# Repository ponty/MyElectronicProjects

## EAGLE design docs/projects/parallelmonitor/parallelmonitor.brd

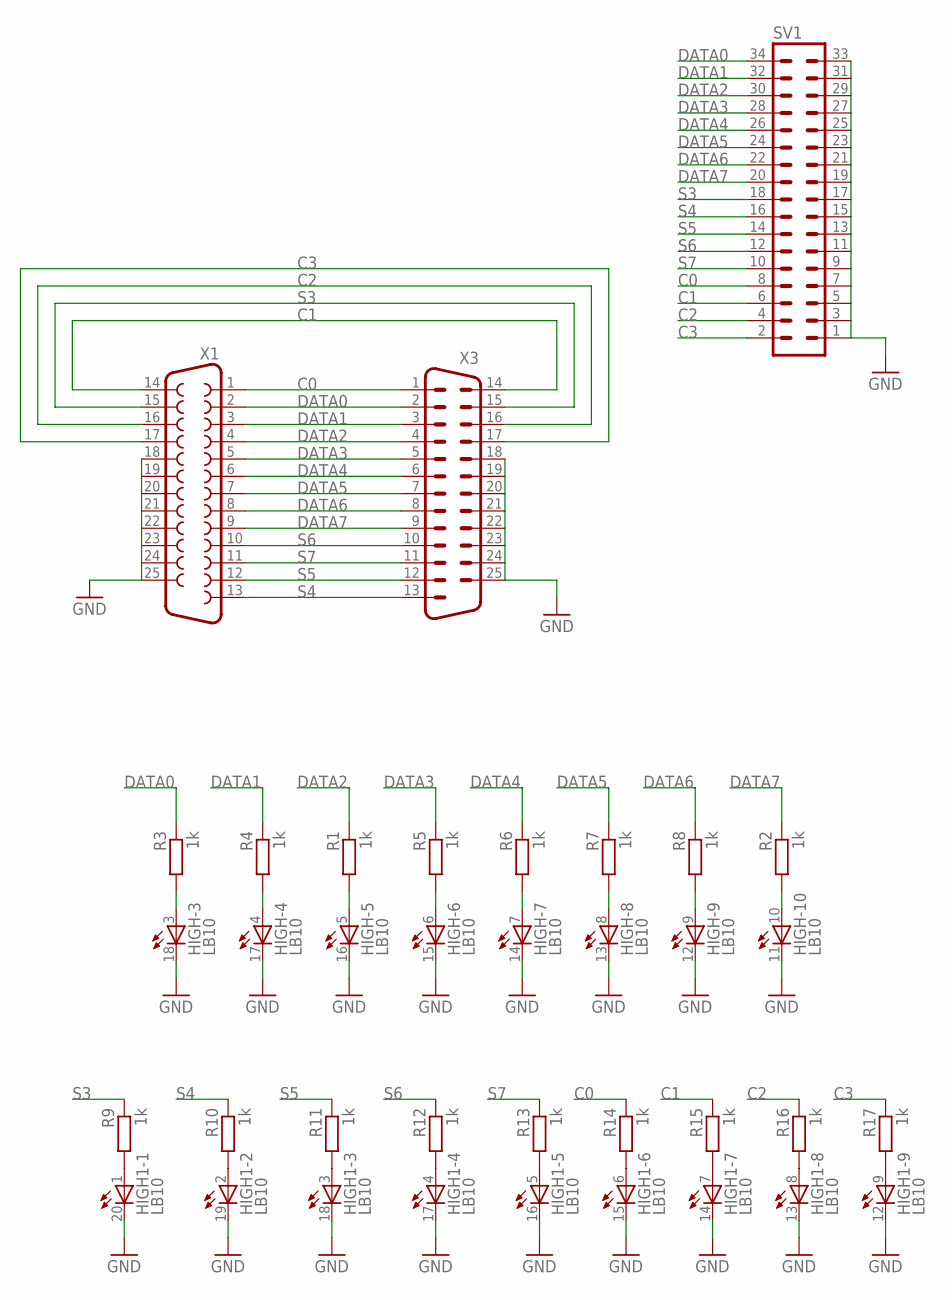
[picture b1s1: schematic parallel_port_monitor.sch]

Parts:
HIGH, HIGH1: LB10
R1, R2, R3, R4, R5, R6, R7, R8, R9, R10, R11, R12, R13, R14, R15, R16, R17: 1k; M0805
SV1: MA17-2W
X1: F25D
X3: M25D

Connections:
C0: R14.1, SV1.8, X1.1, X3.1
C1: R15.1, SV1.6, X1.14, X3.14
C2: R16.1, SV1.4, X1.16, X3.16
C3: R17.1, SV1.2, X1.17, X3.17
DATA0: R3.1, SV1.34, X1.2, X3.2
DATA1: R4.1, SV1.32, X1.3, X3.3
DATA2: R1.1, SV1.30, X1.4, X3.4
DATA3: R5.1, SV1.28, X1.5, X3.5
DATA4: R6.1, SV1.26, X1.6, X3.6
DATA5: R7.1, SV1.24, X1.7, X3.7
DATA6: R8.1, SV1.22, X1.8, X3.8
DATA7: R2.1, SV1.20, X1.9, X3.9
GND: HIGH.11 (C), HIGH.12 (C), HIGH.13 (C), HIGH.14 (C), HIGH.15 (C), HIGH.16 (C), HIGH.17 (C), HIGH.18 (C), HIGH1.12 (C), HIGH1.13 (C), HIGH1.14 (C), HIGH1.15 (C), HIGH1.16 (C), HIGH1.17 (C), HIGH1.18 (C), HIGH1.19 (C), HIGH1.20 (C), SV1.1, SV1.3, SV1.5, SV1.7, SV1.9, SV1.11, SV1.13, SV1.15, SV1.17, SV1.19, SV1.21, SV1.23, SV1.25, SV1.27, SV1.29, SV1.31, SV1.33, X1.18, X1.19, X1.20, X1.21, X1.22, X1.23, X1.24, X1.25, X3.18, X3.19, X3.20, X3.21, X3.22, X3.23, X3.24, X3.25
unnamed: HIGH.10 (A), R2.2
unnamed: HIGH1.1 (A), R9.2
unnamed: HIGH.3 (A), R3.2
unnamed: HIGH.4 (A), R4.2
unnamed: HIGH.6 (A), R5.2
unnamed: HIGH.5 (A), R1.2
unnamed: HIGH.7 (A), R6.2
unnamed: HIGH.8 (A), R7.2
unnamed: HIGH.9 (A), R8.2
unnamed: HIGH1.2 (A), R10.2
unnamed: HIGH1.3 (A), R11.2
unnamed: HIGH1.4 (A), R12.2
unnamed: HIGH1.5 (A), R13.2
unnamed: HIGH1.6 (A), R14.2
unnamed: HIGH1.7 (A), R15.2
unnamed: HIGH1.8 (A), R16.2
unnamed: HIGH1.9 (A), R17.2
S3: R9.1, SV1.18, X1.15, X3.15
S4: R10.1, SV1.16, X1.13, X3.13
S5: R11.1, SV1.14, X1.12, X3.12
S6: R12.1, SV1.12, X1.10, X3.10
S7: R13.1, SV1.10, X1.11, X3.11

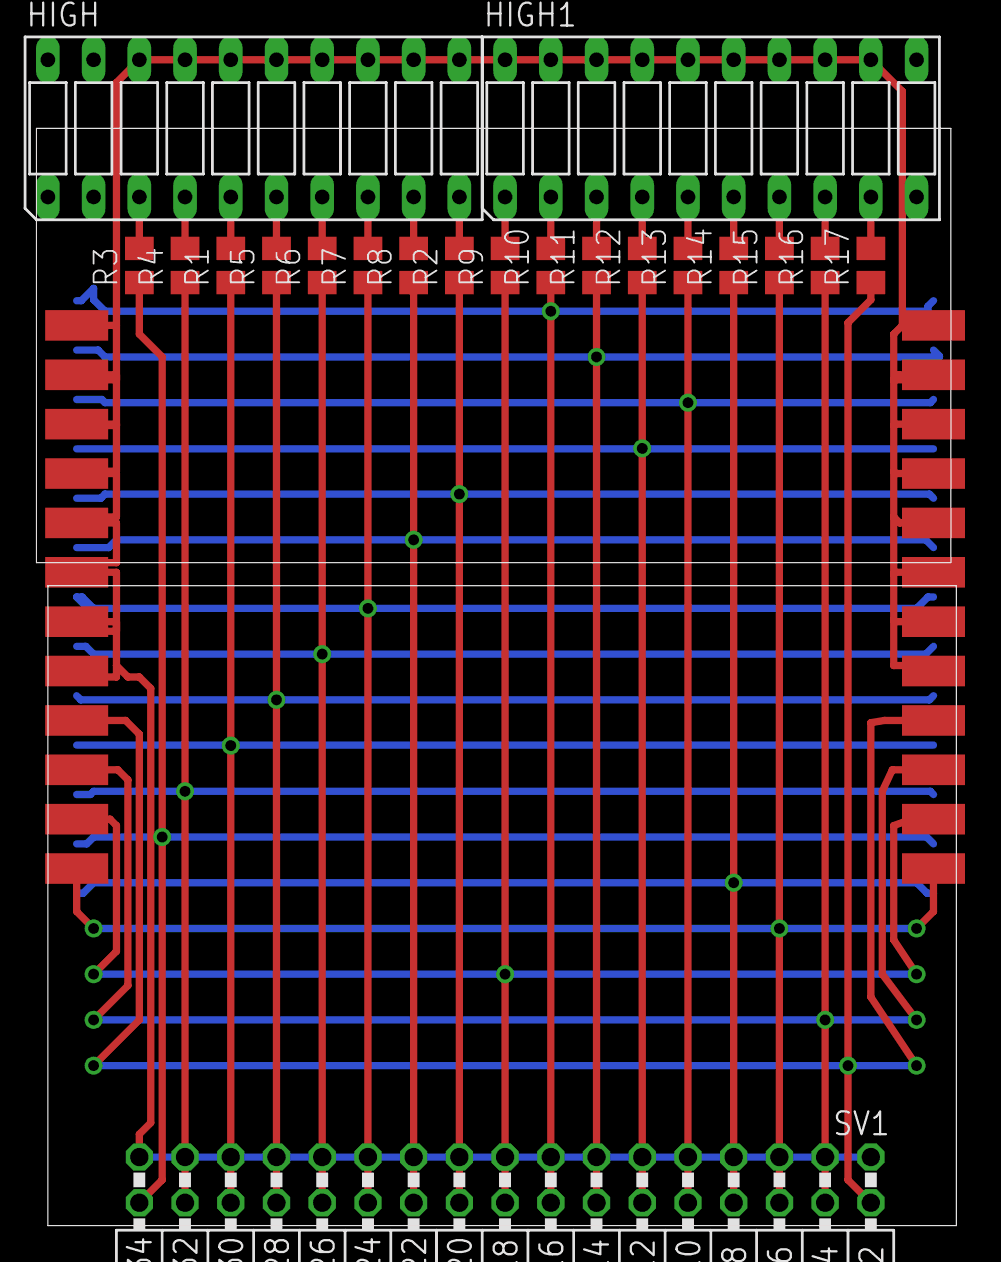
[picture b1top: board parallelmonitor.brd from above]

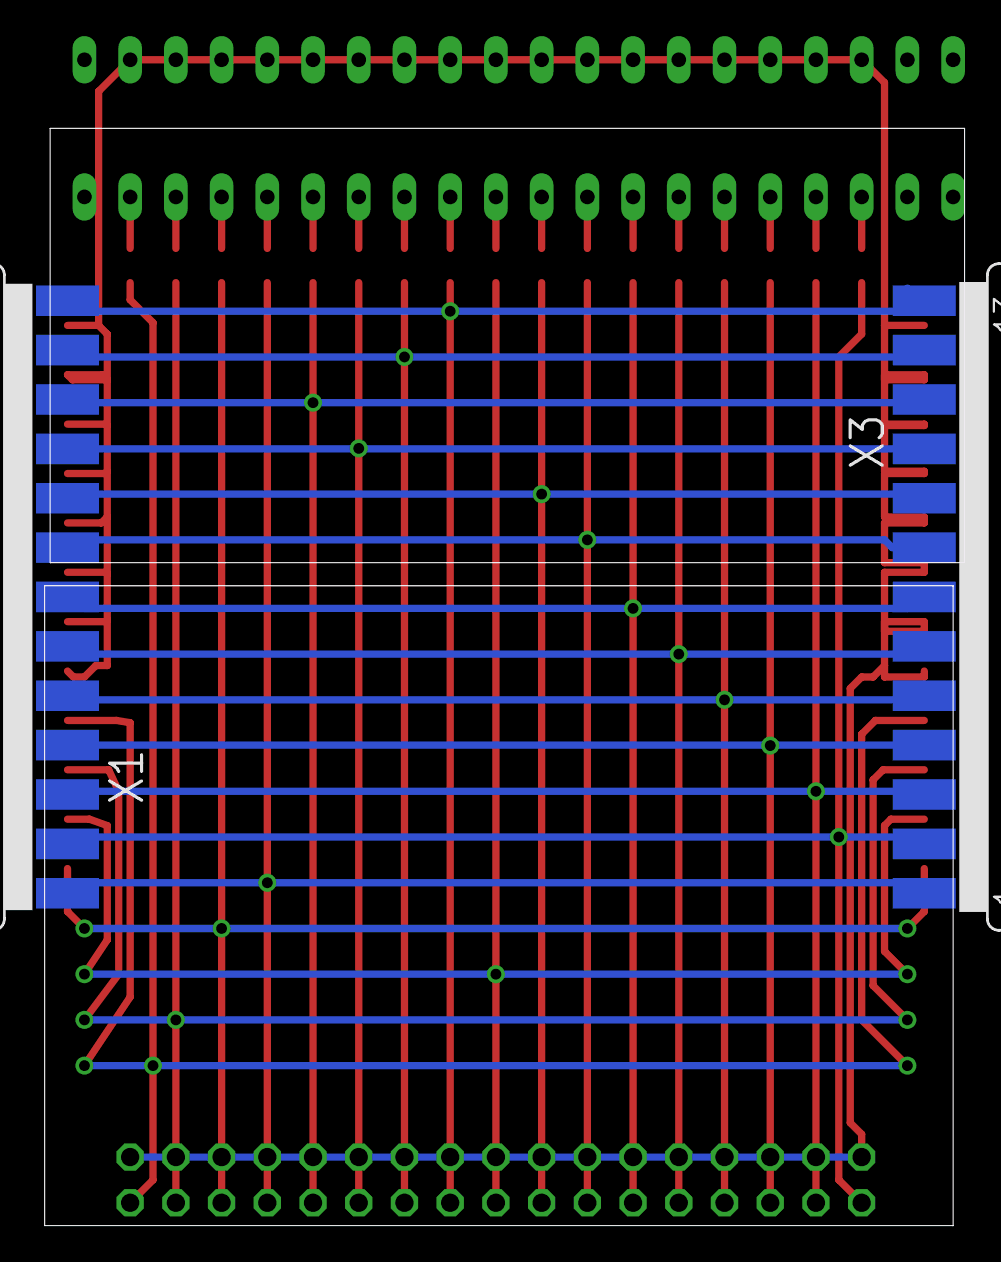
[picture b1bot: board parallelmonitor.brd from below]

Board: 2 copper layers, 51.1 x 61.0 mm, 22 parts (2 on the bottom side), 35 nets.

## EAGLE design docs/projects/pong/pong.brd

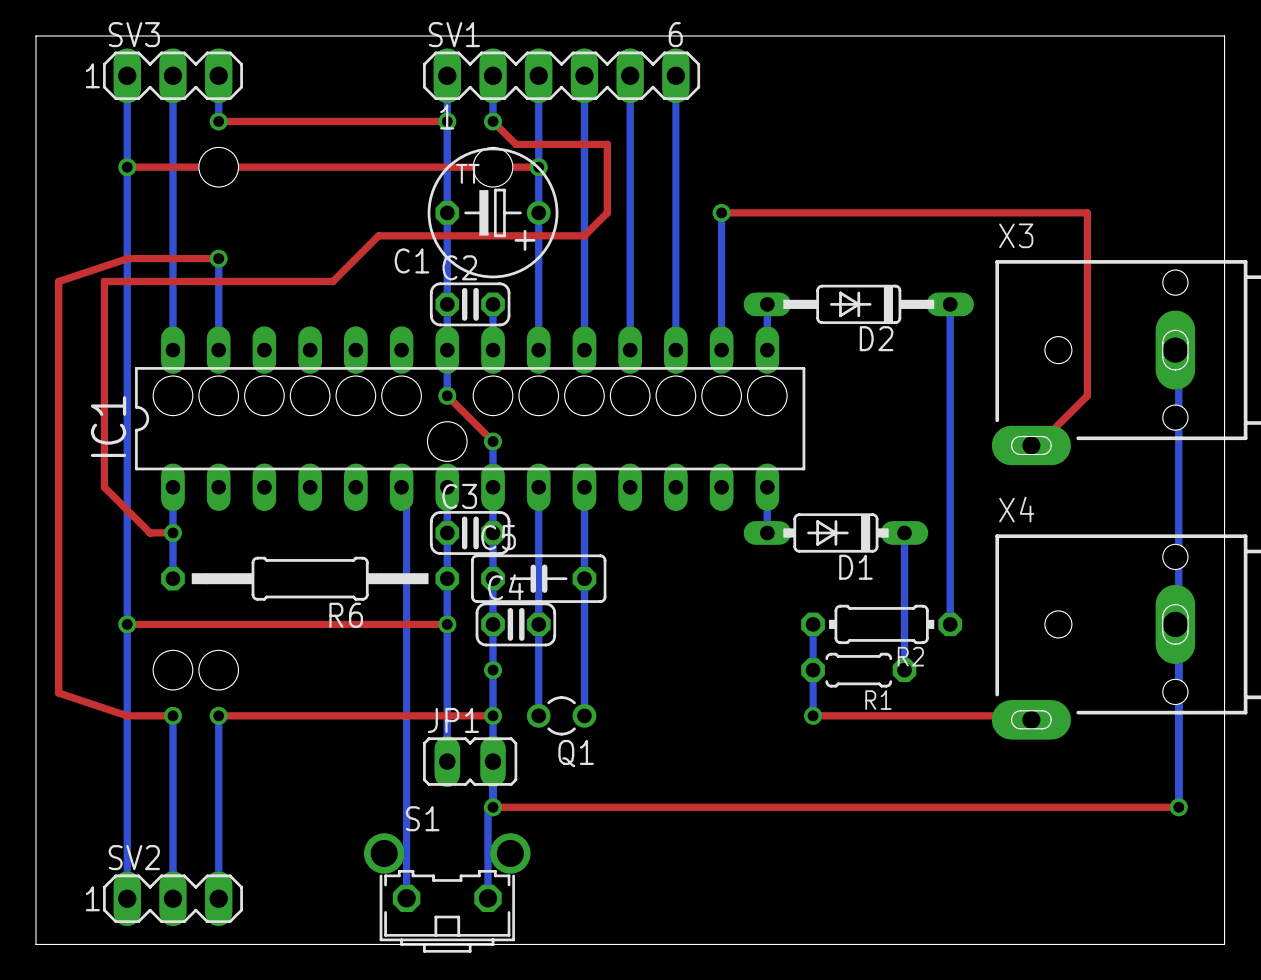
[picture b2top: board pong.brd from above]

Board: 2 copper layers, 66.0 x 50.5 mm, 19 parts (0 on the bottom side), 18 nets.

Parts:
C1: 4u7; TT5D7
C2, C3: 100n; C025-024X044
C4: 22p; C025-024X044
C5: 22p; C050-025X075
D1: 1N4148DO35-7; DO35-7
D2: 1N4148DO35-10; DO35-10
IC1: DIL28-3
JP1: JP1
Q1: 20MHz; TC26V
R1: 330; 0204/5
R2: 1k; 0204/7
R6: 10k; 0207/15
S1: B3F-31XX
SV1: ISP; MA06-1
SV2: POT1; MA03-1
SV3: POT2; MA03-1
X3: AUDIO; WBTOR1
X4: VIDEO; WBTOR1

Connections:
+5V: C1.+, C3.1, IC1.7, IC1.20, JP1.1, R6.1, SV1.3, SV2.1, SV3.1
GND: C1.-, C2.1, C3.2, C4.1, C5.1, IC1.8, IC1.22, JP1.2, S1.2, SV1.1, SV2.3, SV3.3, X3.S, X4.S
MISO: IC1.18, SV1.5
MOSI: IC1.17, SV1.6
unnamed: C2.2, IC1.21
unnamed: D1.A, IC1.14
unnamed: IC1.27, SV2.2
unnamed: IC1.28, SV3.2
unnamed: D2.A, IC1.15
unnamed: D1.C, R1.1
unnamed: D2.C, R2.1
unnamed: IC1.6, S1.1
unnamed: R1.2, R2.2, X4.T
unnamed: IC1.16, X3.T
unnamed: C4.2, IC1.9, Q1.2
unnamed: C5.2, IC1.10, Q1.1
RST: IC1.1, R6.2, SV1.2
SCK: IC1.19, SV1.4

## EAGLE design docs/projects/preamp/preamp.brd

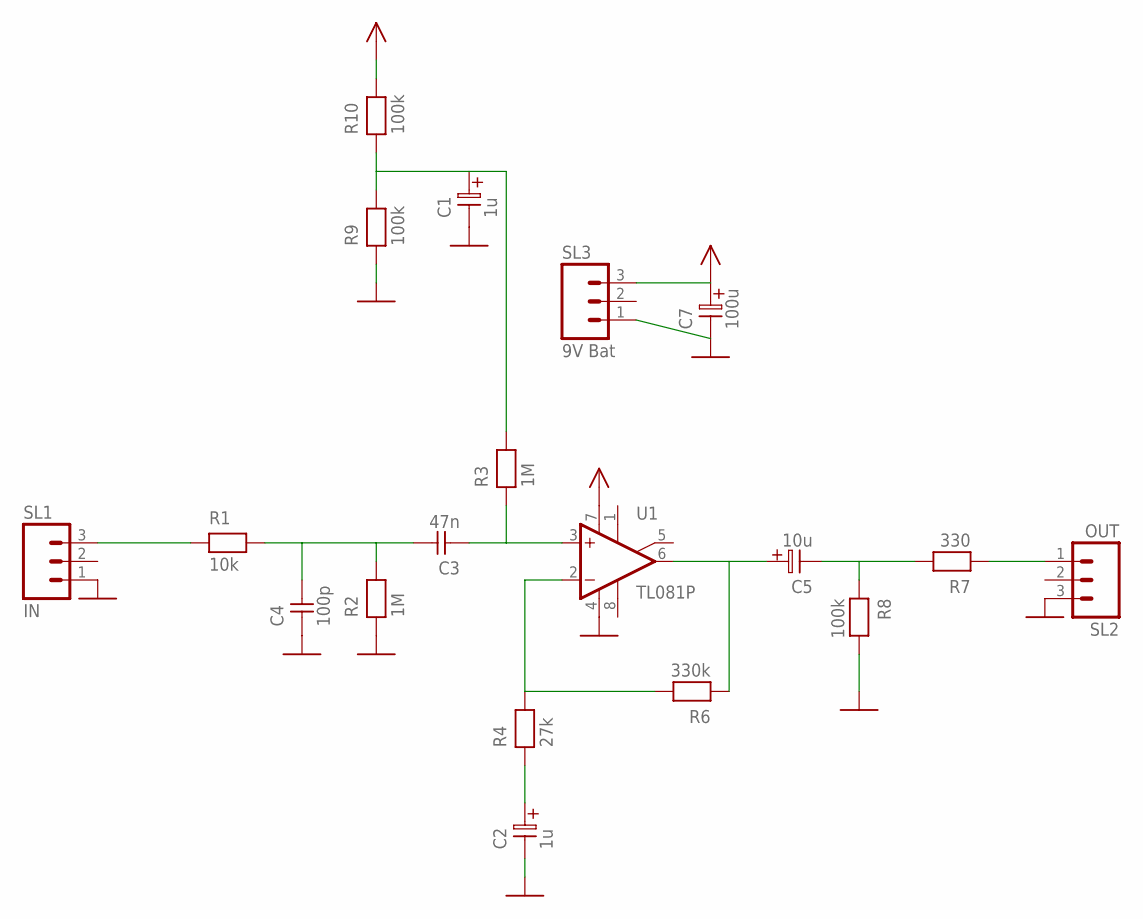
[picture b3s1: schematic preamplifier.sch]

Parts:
C1, C2: 1u; ES-2,5L
C3: 47n; C-5
C4: 100p; C-5
C5: 10u; ES-2,5L
C7: 100u; ES-2,5L
R1: 10k; R-10
R2, R3: 1M; R-10
R4: 27k; R-10
R6: 330k; R-10
R7: 330; R-10
R8, R9, R10: 100k; R-10
SL1: IN; 03P
SL2: OUT; 03P
SL3: 9V Bat; 03P
U1: TL081P; DIL08

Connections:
GND: C1.2, C2.2, C4.1, C7.2, R2.1, R8.2, R9.1, SL1.1, SL2.3, SL3.1, U1.4 (V-)
unnamed: C3.2, C4.2, R1.2, R2.2
unnamed: C3.1, R3.1, U1.3 (+IN)
unnamed: R1.1, SL1.3
unnamed: R4.2, R6.2, U1.2 (-IN)
unnamed: C5.1, R6.1, U1.6 (OUT)
unnamed: C5.2, R7.2, R8.1
unnamed: C2.1, R4.1
unnamed: R7.1, SL2.1
unnamed: C1.1, R3.2, R9.2, R10.1
VCC: C7.1, R10.2, SL3.3, U1.7 (V+)

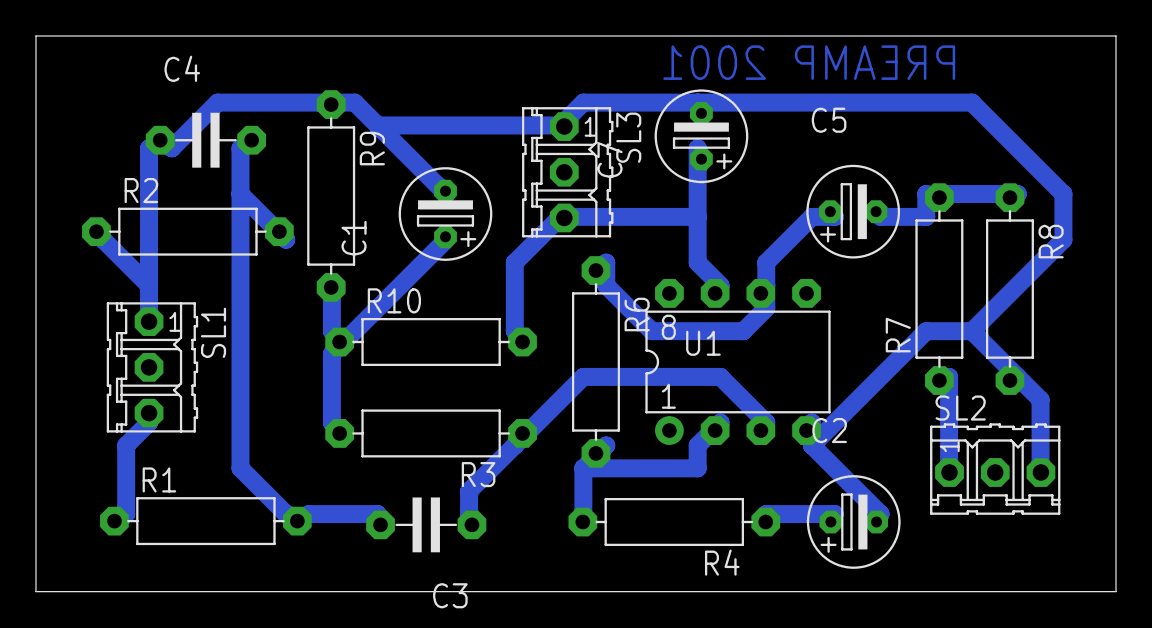
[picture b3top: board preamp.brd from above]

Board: 1 copper layer, 60.0 x 30.9 mm, 19 parts (0 on the bottom side), 11 nets.

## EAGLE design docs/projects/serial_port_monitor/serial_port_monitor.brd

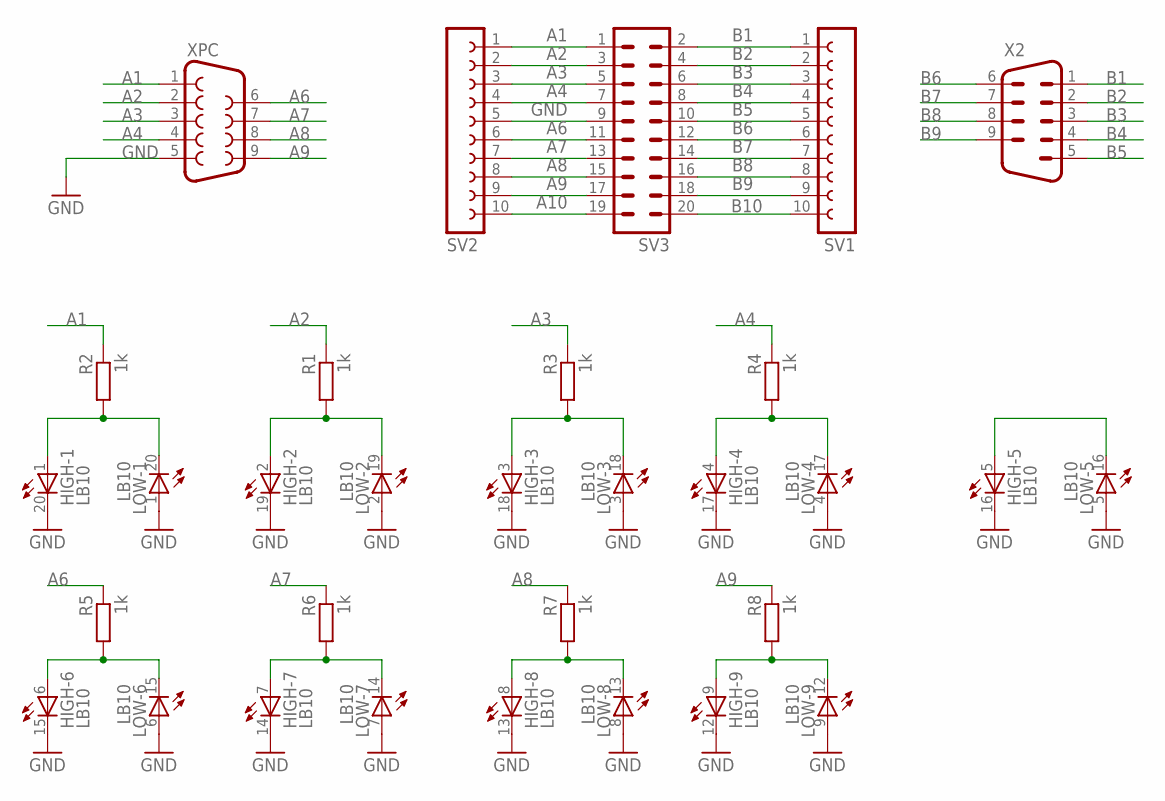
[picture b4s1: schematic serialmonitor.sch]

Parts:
HIGH: LB10
LOW: LB10
R1, R2, R3, R4, R5, R6, R7, R8: 1k; M0805
SV1, SV2: FE10-1; FE10
SV3: MA10-2
X2: M09D
XPC: F09D

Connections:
A1: R2.1, SV2.1, SV3.1, XPC.1
A2: R1.1, SV2.2, SV3.3, XPC.2
A3: R3.1, SV2.3, SV3.5, XPC.3
A4: R4.1, SV2.4, SV3.7, XPC.4
A6: R5.1, SV2.6, SV3.11, XPC.6
A7: R6.1, SV2.7, SV3.13, XPC.7
A8: R7.1, SV2.8, SV3.15, XPC.8
A9: R8.1, SV2.9, SV3.17, XPC.9
A10: SV2.10, SV3.19
B1: SV1.1, SV3.2, X2.1
B2: SV1.2, SV3.4, X2.2
B3: SV1.3, SV3.6, X2.3
B4: SV1.4, SV3.8, X2.4
B5: SV1.5, SV3.10, X2.5
B6: SV1.6, SV3.12, X2.6
B7: SV1.7, SV3.14, X2.7
B8: SV1.8, SV3.16, X2.8
B9: SV1.9, SV3.18, X2.9
B10: SV1.10, SV3.20
GND: HIGH.12 (C), HIGH.13 (C), HIGH.14 (C), HIGH.15 (C), HIGH.16 (C), HIGH.17 (C), HIGH.18 (C), HIGH.19 (C), HIGH.20 (C), LOW.1 (A), LOW.2 (A), LOW.3 (A), LOW.4 (A), LOW.5 (A), LOW.6 (A), LOW.7 (A), LOW.8 (A), LOW.9 (A), SV2.5, SV3.9, XPC.5
unnamed: HIGH.1 (A), LOW.20 (C), R2.2
unnamed: HIGH.2 (A), LOW.19 (C), R1.2
unnamed: HIGH.3 (A), LOW.18 (C), R3.2
unnamed: HIGH.4 (A), LOW.17 (C), R4.2
unnamed: HIGH.6 (A), LOW.15 (C), R5.2
unnamed: HIGH.5 (A), LOW.16 (C)
unnamed: HIGH.7 (A), LOW.14 (C), R6.2
unnamed: HIGH.8 (A), LOW.13 (C), R7.2
unnamed: HIGH.9 (A), LOW.12 (C), R8.2

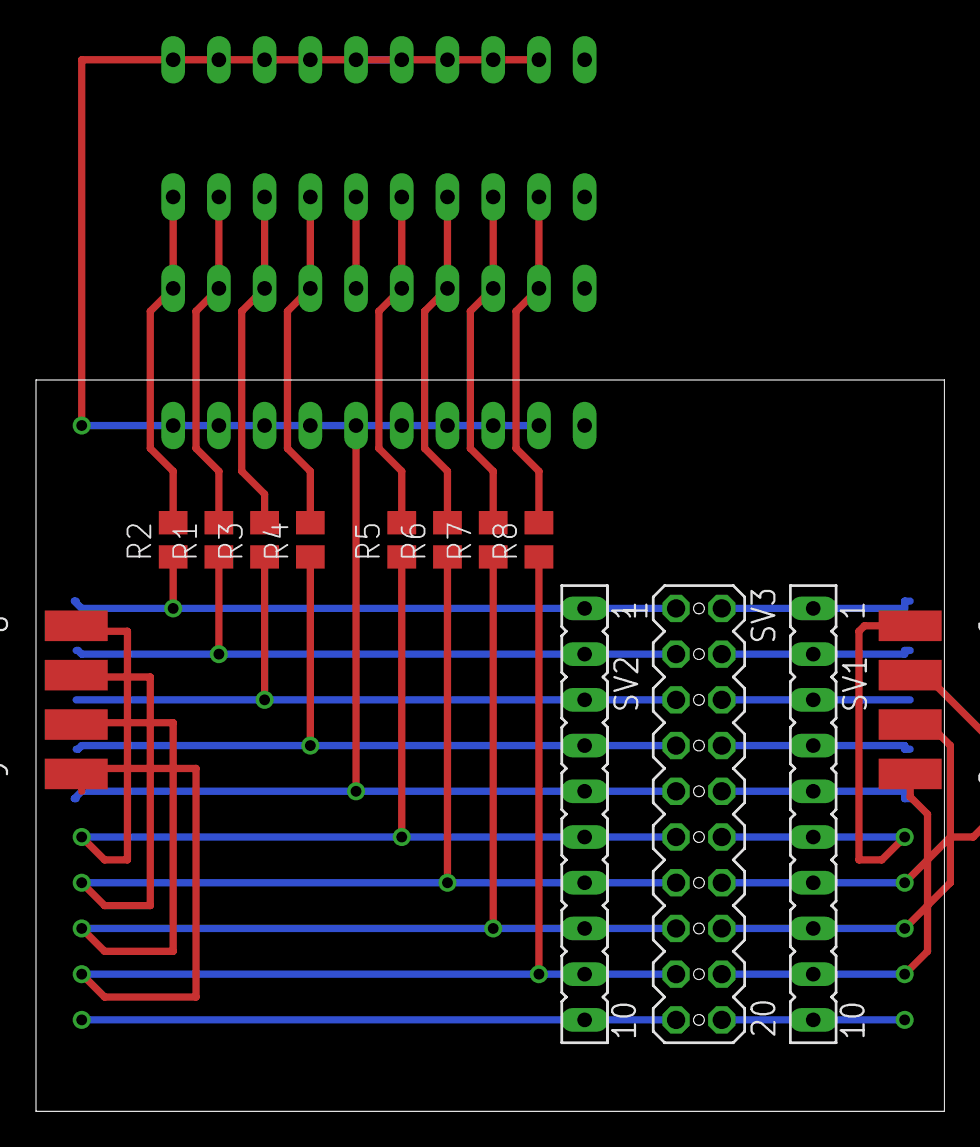
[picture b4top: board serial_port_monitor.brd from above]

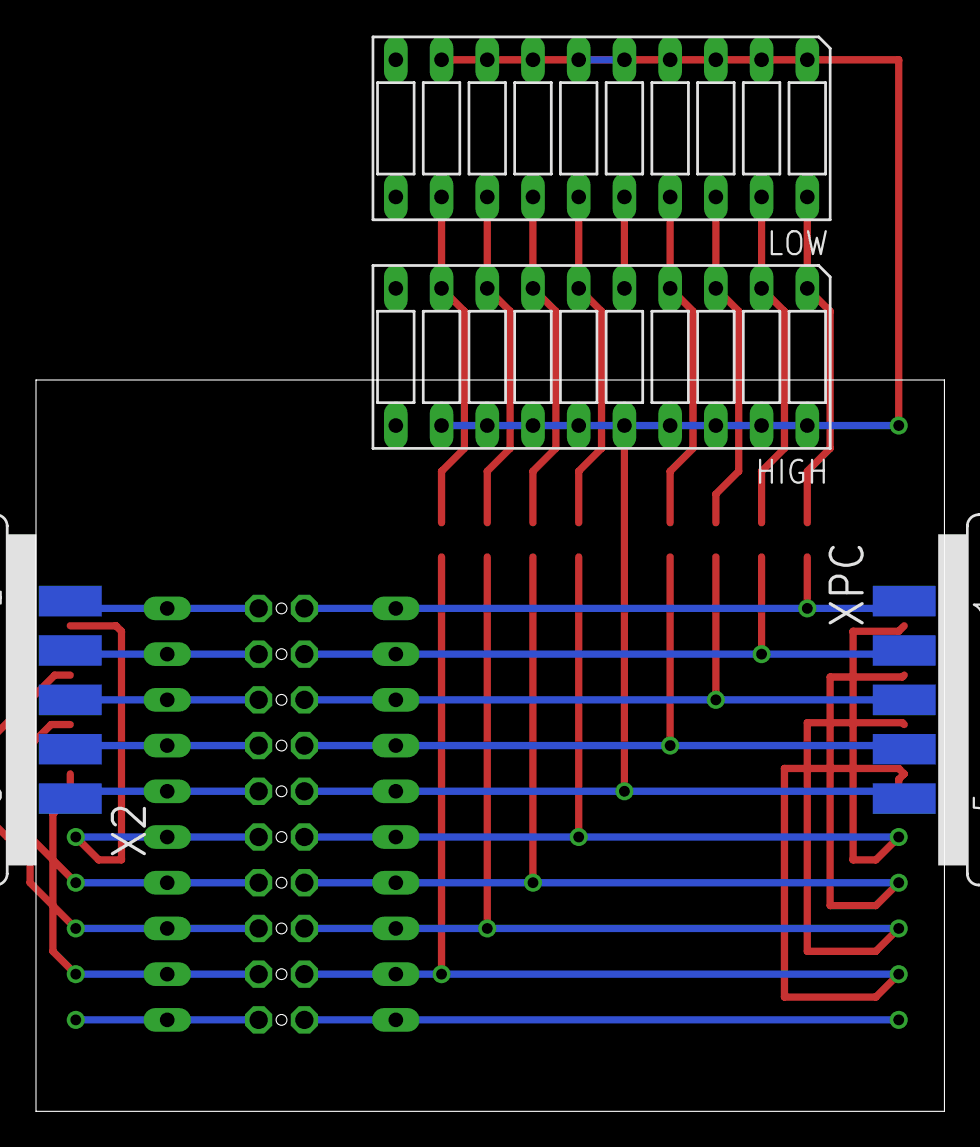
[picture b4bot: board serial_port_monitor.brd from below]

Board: 2 copper layers, 50.5 x 40.6 mm, 15 parts (4 on the bottom side), 29 nets.

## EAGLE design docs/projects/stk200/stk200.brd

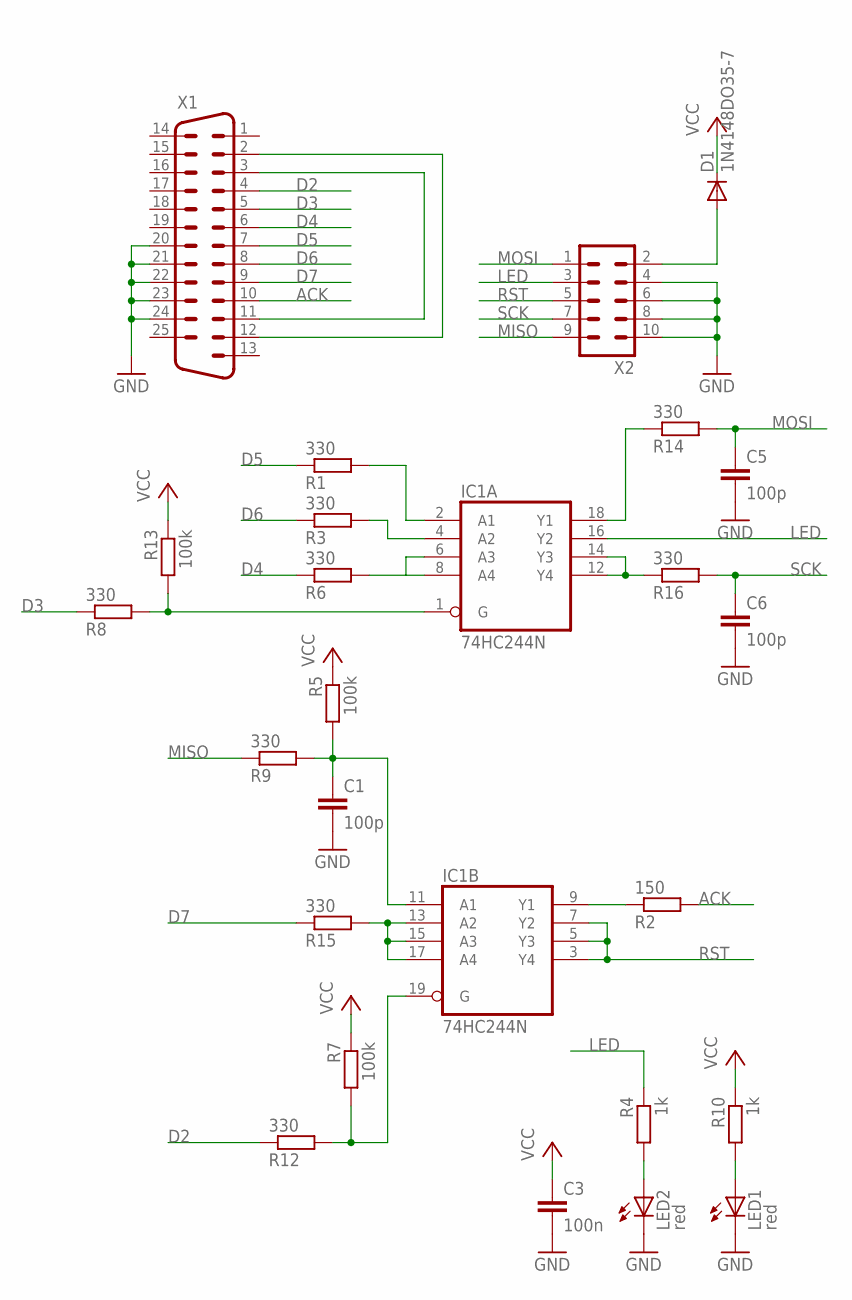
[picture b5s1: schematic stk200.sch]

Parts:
C1: 100p; C025-024X044
C3: 100n; C025-024X044
C5, C6: 100p; C102-043X133
D1: 1N4148DO35-7; DO35-7
IC1: 74HC244N; DIL20
LED1, LED2: red; LED3MM
R1, R12: 330; 0207/10
R2: 150; 0207/15
R3, R6, R14: 330; 0204V
R4: 1k; 0207/15
R5: 100k; 0617/22
R7: 100k; 0204V
R8: 330; 0617/17
R9, R16: 330; 0204/5
R10: 1k; 0204/5
R13: 100k; M1206
R15: 330; 0207/12
X1: M25D
X2: ML10L

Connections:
ACK: R2.2, X1.10
D2: R12.1, X1.4
D3: R8.1, X1.5
D4: R6.1, X1.6
D5: R1.1, X1.7
D6: R3.1, X1.8
D7: R15.1, X1.9
GND: C1.2, C3.2, C5.2, C6.2, IC1.10 (GND), LED1.K (C), LED2.K (C), X1.20, X1.21, X1.22, X1.23, X1.24, X2.4, X2.6, X2.8, X2.10
LED: IC1.16 (Y2), R4.1, X2.3
MISO: R9.1, X2.9
MOSI: C5.1, R14.2, X2.1
unnamed: LED1.A, R10.2
unnamed: IC1.6 (A3), IC1.8 (A4), R6.2
unnamed: D1.A, X2.2
unnamed: IC1.13 (A2), IC1.15 (A3), IC1.17 (A4), R15.2
unnamed: X1.2, X1.12
unnamed: IC1.12 (Y4), IC1.14 (Y3), R16.1
unnamed: IC1.18 (Y1), R14.1
unnamed: IC1.9 (Y1), R2.1
unnamed: IC1.19 (G), R7.2, R12.2
unnamed: IC1.4 (A2), R3.2
unnamed: IC1.2 (A1), R1.2
unnamed: IC1.1 (G), R8.2, R13.2
unnamed: LED2.A, R4.2
unnamed: C1.1, IC1.11 (A1), R5.2, R9.2
unnamed: X1.3, X1.11
RST: IC1.3 (Y4), IC1.5 (Y3), IC1.7 (Y2), X2.5
SCK: C6.1, R16.2, X2.7
VCC: C3.1, D1.C, IC1.20 (VCC), R5.1, R7.1, R10.1, R13.1

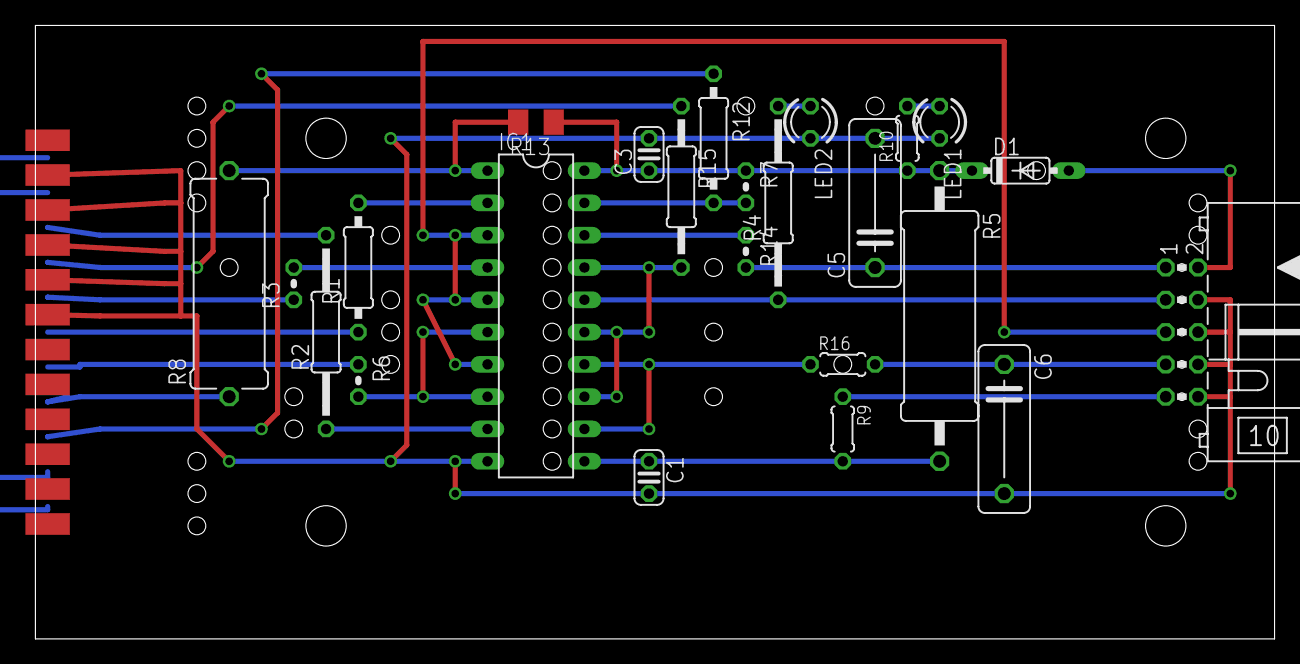
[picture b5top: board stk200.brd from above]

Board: 2 copper layers, 97.5 x 48.2 mm, 25 parts (1 on the bottom side), 29 nets.

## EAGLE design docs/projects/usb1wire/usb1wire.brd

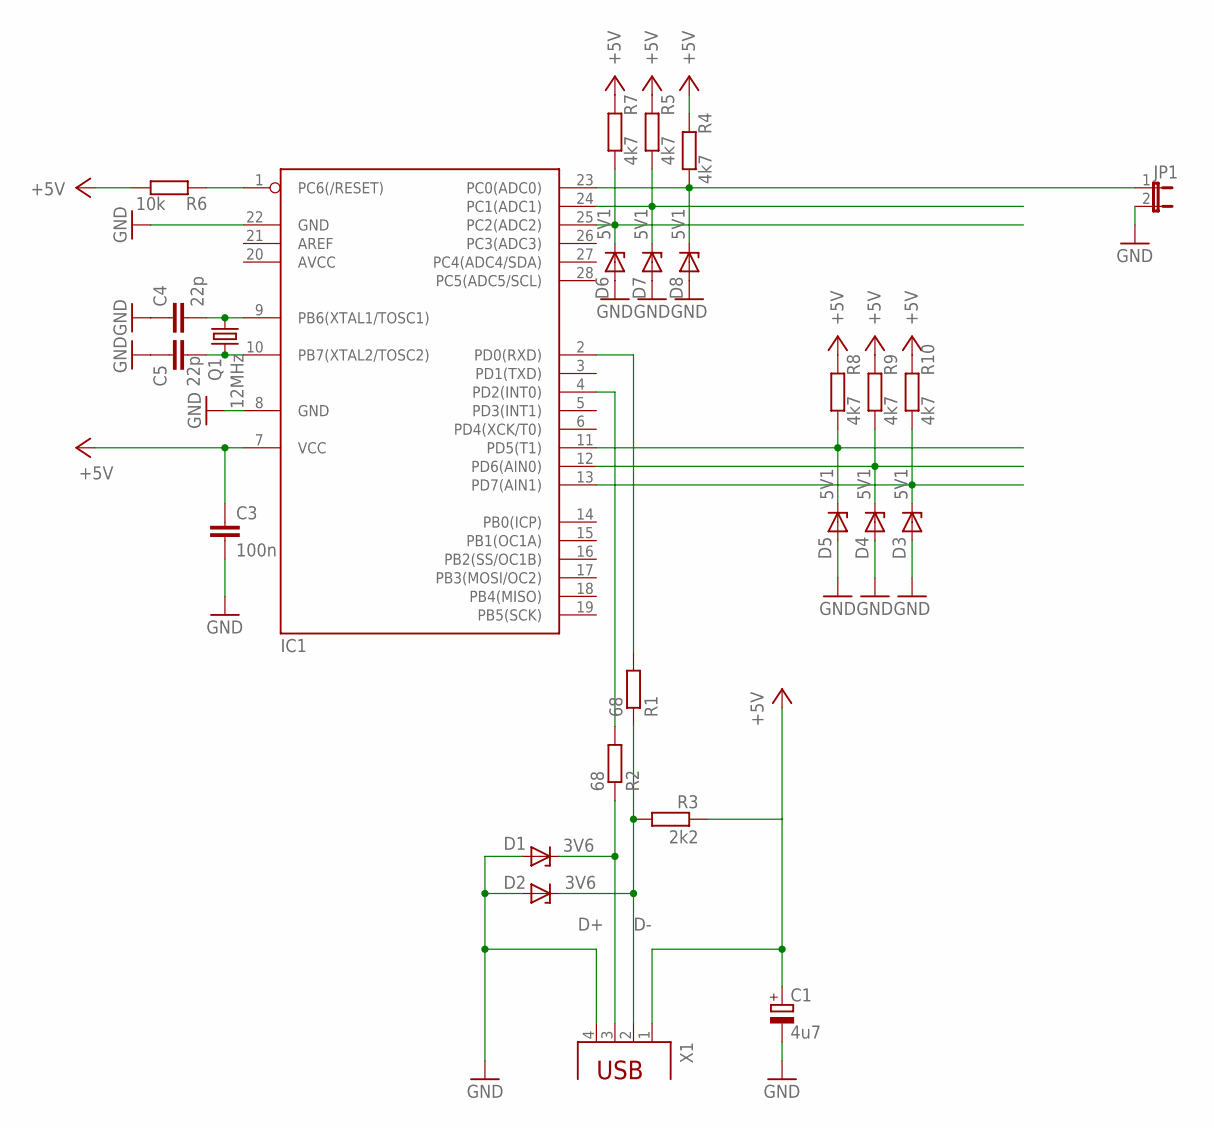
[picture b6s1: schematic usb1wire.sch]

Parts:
C1: 4u7; TT2D4
C3: 100n; C025-024X044
C4: 22p; C025-024X044
C5: 22p; C050-025X075
D1: 3V6; DO34Z7
D2: 3V6; ZDIO-5
D3: 5V1; ZDIO-5
D4: 5V1; DO34Z7
D5: 5V1; DO41Z10
D6, D7, D8: 5V1; SOD80C
IC1: MEGA8-P; DIL28-3
JP1: JP1E; JP1
Q1: 12MHz; TC26V
R1: 68; 0207/10
R2: 68; 0204V
R3: 2k2; 0207/2V
R4: 4k7; 0207/15
R5, R8: 4k7; 0207/12
R6: 10k; 0207/15
R7, R9: 4k7; 0207/10
R10: 4k7; 0204/7
X1: PN61729

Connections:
+5V: C1.+, C3.1, IC1.7 (VCC), R3.1, R4.2, R5.2, R6.1, R7.2, R8.2, R9.2, R10.2, X1.1
AVCC: IC1.20 (AVCC)
D+: D1.C, R2.1, X1.3
D-: D2.C, R1.1, R3.2, X1.2
GND: C1.-, C3.2, C4.1, C5.1, D1.A, D2.A, D3.A, D4.A, D5.A, D6.A, D7.A, D8.A, IC1.8 (GND), IC1.22 (GND), JP1.2, X1.4
unnamed: IC1.1 (PC6(/RESET)), R6.2
unnamed: IC1.2 (PD0(RXD)), R1.2
unnamed: IC1.4 (PD2(INT0)), R2.2
unnamed: D8.C, IC1.23 (PC0(ADC0)), JP1.1, R4.1
unnamed: D3.C, IC1.13 (PD7(AIN1)), R10.1
unnamed: D7.C, IC1.24 (PC1(ADC1)), R5.1
unnamed: D6.C, IC1.25 (PC2(ADC2)), R7.1
unnamed: D4.C, IC1.12 (PD6(AIN0)), R9.1
unnamed: D5.C, IC1.11 (PD5(T1)), R8.1
unnamed: C4.2, IC1.9 (PB6(XTAL1/TOSC1)), Q1.2
unnamed: C5.2, IC1.10 (PB7(XTAL2/TOSC2)), Q1.1

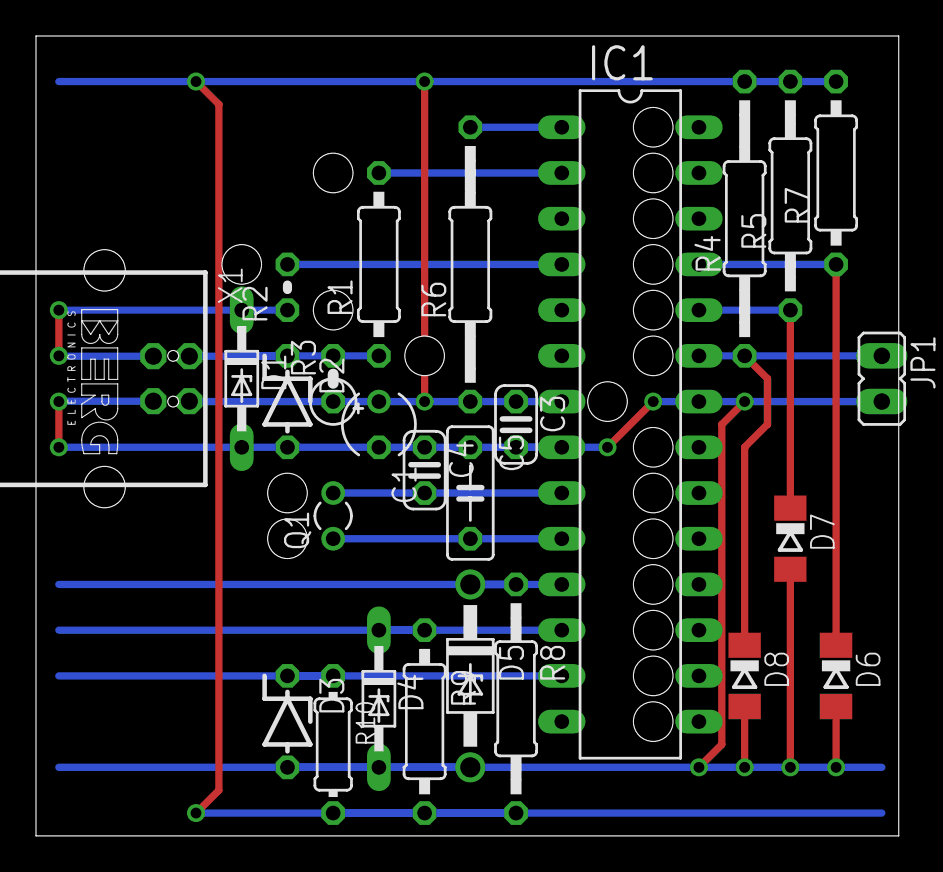
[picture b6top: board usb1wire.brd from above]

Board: 2 copper layers, 47.9 x 44.4 mm, 26 parts (0 on the bottom side), 15 nets.
